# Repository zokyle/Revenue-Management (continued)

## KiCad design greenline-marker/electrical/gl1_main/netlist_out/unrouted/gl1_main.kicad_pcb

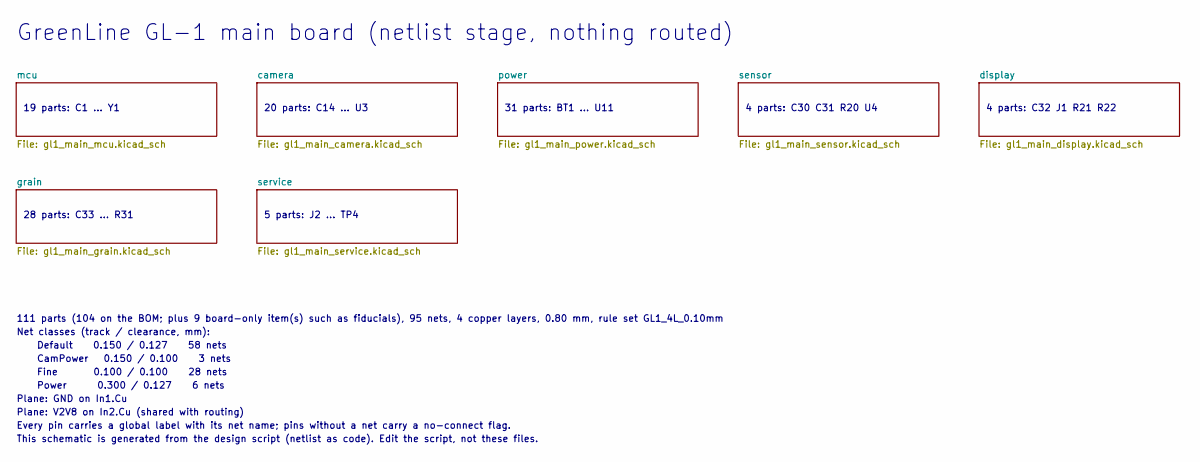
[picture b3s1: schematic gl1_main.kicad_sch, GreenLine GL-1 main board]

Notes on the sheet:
GreenLine GL-1 main board (netlist stage, nothing routed)
19 parts: C1 ... Y1
20 parts: C14 ... U3
31 parts: BT1 ... U11
4 parts: C30 C31 R20 U4
4 parts: C32 J1 R21 R22
28 parts: C33 ... R31
5 parts: J2 ... TP4
111 parts (104 on the BOM; plus 9 board-only item(s) such as fiducials), 95 nets, 4 copper layers, 0.80 mm, rule set GL1_4L_0.10mm
Net classes (track / clearance, mm):
Default 0.150 / 0.127 58 nets
CamPower 0.150 / 0.100 3 nets
Fine 0.100 / 0.100 28 nets
Power 0.300 / 0.127 6 nets
Plane: GND on In1.Cu
Plane: V2V8 on In2.Cu (shared with routing)
Every pin carries a global label with its net name; pins without a net carry a no-connect flag.
This schematic is generated from the design script (netlist as code). Edit the script, not these files.

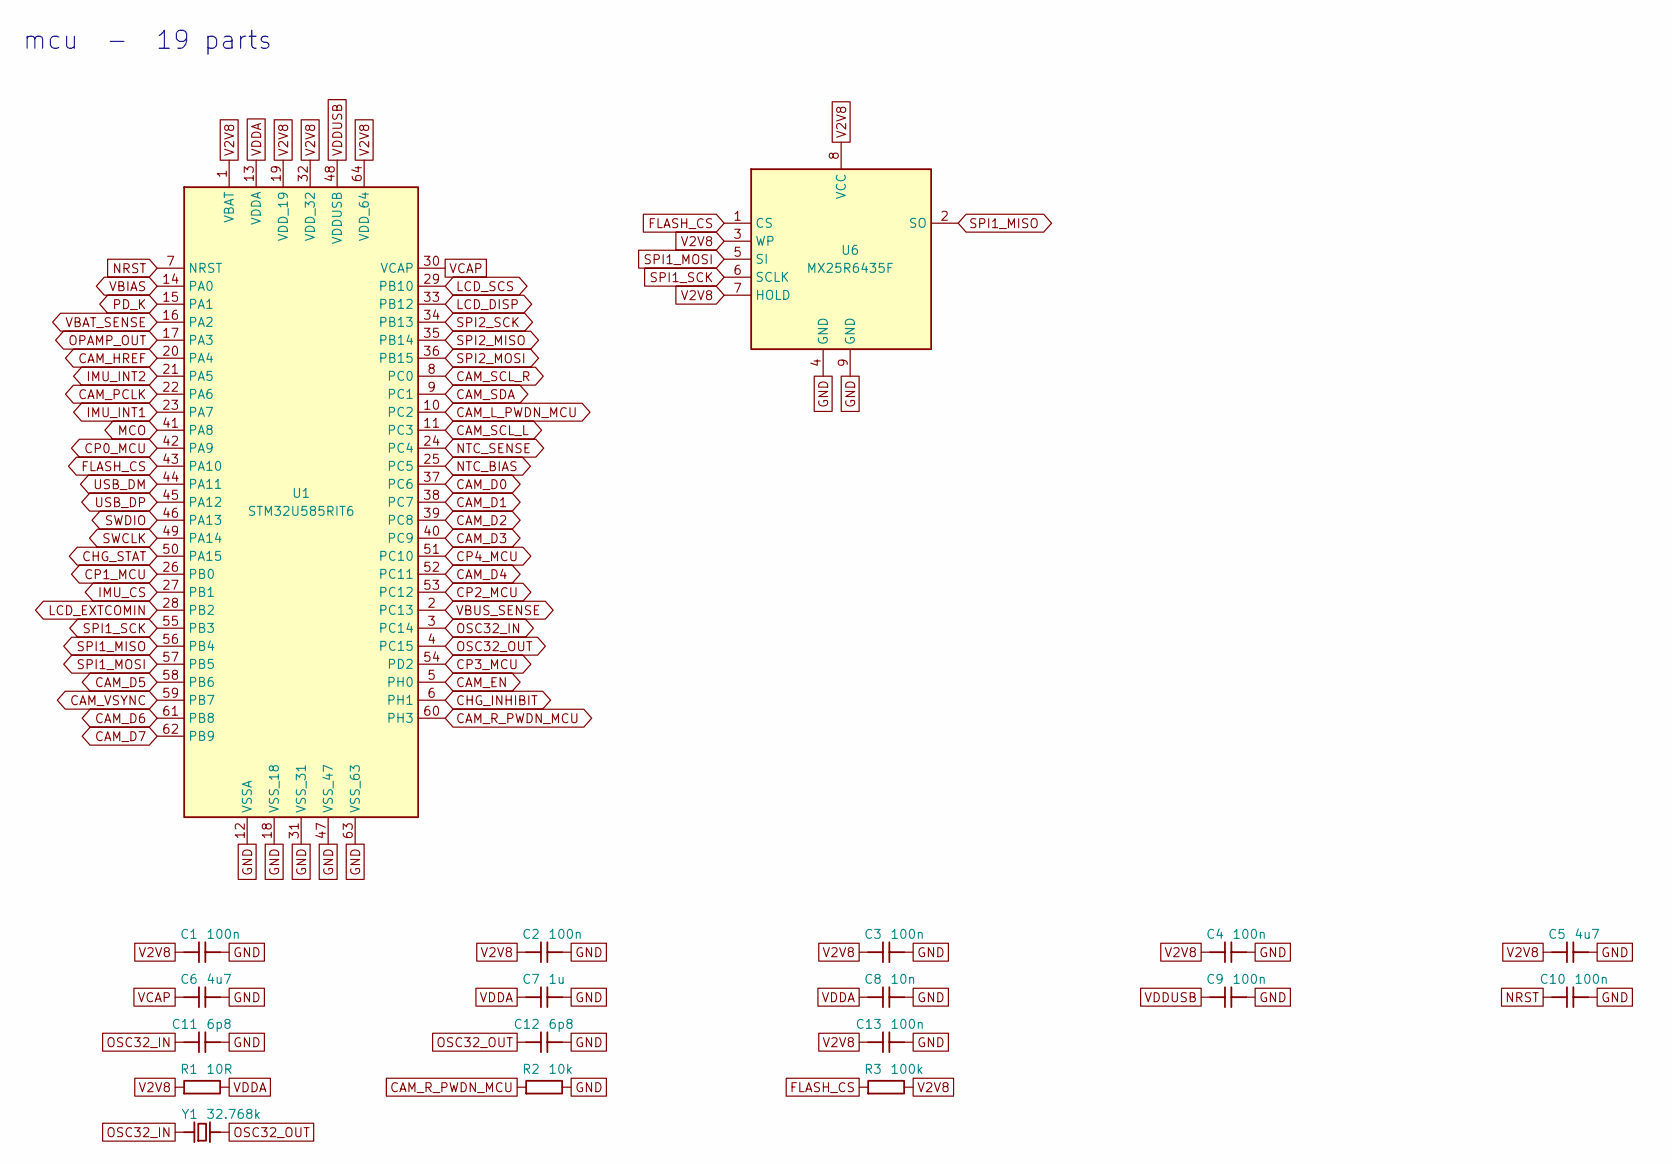
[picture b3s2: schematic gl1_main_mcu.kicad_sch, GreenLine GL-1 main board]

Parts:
C1, C2, C3, C4, C9, C10, C13: 100n; C_0402_1005Metric; MPN GRM155R71C104KA88D
C5, C6: 4u7; C_0402_1005Metric; MPN GRM155R60J475ME47D
C7: 1u; C_0402_1005Metric; MPN GRM155R61A105KE15D
C8: 10n; C_0402_1005Metric; MPN GRM155R71H103KA88D
C11, C12: 6p8; C_0402_1005Metric; MPN GRM1555C1H6R8CA01D
R1: 10R; R_0402_1005Metric; MPN RC0402FR-0710RL
R2: 10k; R_0402_1005Metric; MPN RC0402FR-0710KL
R3: 100k; R_0402_1005Metric; MPN RC0402FR-07100KL
U1: STM32U585RIT6; LQFP-64_10x10mm_P0.5mm; MPN STM32U585RIT6
U6: MX25R6435F; WSON-8-1EP_6x5mm_P1.27mm_EP3.4x4mm; MPN MX25R6435FZNIL0
Y1: 32.768k; Crystal_SMD_3215-2Pin_3.2x1.5mm; MPN ABS07-120-32.768KHZ-T

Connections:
CAM_D0: U1.37 (PC6); also elsewhere on the board
CAM_D1: U1.38 (PC7); also elsewhere on the board
CAM_D2: U1.39 (PC8); also elsewhere on the board
CAM_D3: U1.40 (PC9); also elsewhere on the board
CAM_D4: U1.52 (PC11); also elsewhere on the board
CAM_D5: U1.58 (PB6); also elsewhere on the board
CAM_D6: U1.61 (PB8); also elsewhere on the board
CAM_D7: U1.62 (PB9); also elsewhere on the board
CAM_EN: U1.5 (PH0); also elsewhere on the board
CAM_HREF: U1.20 (PA4); also elsewhere on the board
CAM_L_PWDN_MCU: U1.10 (PC2); also elsewhere on the board
CAM_PCLK: U1.22 (PA6); also elsewhere on the board
CAM_R_PWDN_MCU: R2.1, U1.60 (PH3); also elsewhere on the board
CAM_SCL_L: U1.11 (PC3); also elsewhere on the board
CAM_SCL_R: U1.8 (PC0); also elsewhere on the board
CAM_SDA: U1.9 (PC1); also elsewhere on the board
CAM_VSYNC: U1.59 (PB7); also elsewhere on the board
CHG_INHIBIT: U1.6 (PH1); also elsewhere on the board
CHG_STAT: U1.50 (PA15); also elsewhere on the board
CP0_MCU: U1.42 (PA9); also elsewhere on the board
CP1_MCU: U1.26 (PB0); also elsewhere on the board
CP2_MCU: U1.53 (PC12); also elsewhere on the board
CP3_MCU: U1.54 (PD2); also elsewhere on the board
CP4_MCU: U1.51 (PC10); also elsewhere on the board
FLASH_CS: R3.1, U1.43 (PA10), U6.1 (CS)
GND: C1.2, C2.2, C3.2, C4.2, C5.2, C6.2, C7.2, C8.2, C9.2, C10.2, C11.2, C12.2, C13.2, R2.2, U1.12 (VSSA), U1.18 (VSS_18), U1.31 (VSS_31), U1.47 (VSS_47), U1.63 (VSS_63), U6.4 (GND), U6.9 (GND); also elsewhere on the board
IMU_CS: U1.27 (PB1); also elsewhere on the board
IMU_INT1: U1.23 (PA7); also elsewhere on the board
IMU_INT2: U1.21 (PA5); also elsewhere on the board
LCD_DISP: U1.33 (PB12); also elsewhere on the board
LCD_EXTCOMIN: U1.28 (PB2); also elsewhere on the board
LCD_SCS: U1.29 (PB10); also elsewhere on the board
MCO: U1.41 (PA8); also elsewhere on the board
NRST: C10.1, U1.7 (NRST); also elsewhere on the board
NTC_BIAS: U1.25 (PC5); also elsewhere on the board
NTC_SENSE: U1.24 (PC4); also elsewhere on the board
OPAMP_OUT: U1.17 (PA3); also elsewhere on the board
OSC32_IN: C11.1, U1.3 (PC14), Y1.1
OSC32_OUT: C12.1, U1.4 (PC15), Y1.2
PD_K: U1.15 (PA1); also elsewhere on the board
SPI1_MISO: U1.56 (PB4), U6.2 (SO)
SPI1_MOSI: U1.57 (PB5), U6.5 (SI); also elsewhere on the board
SPI1_SCK: U1.55 (PB3), U6.6 (SCLK); also elsewhere on the board
SPI2_MISO: U1.35 (PB14); also elsewhere on the board
SPI2_MOSI: U1.36 (PB15); also elsewhere on the board
SPI2_SCK: U1.34 (PB13); also elsewhere on the board
SWCLK: U1.49 (PA14); also elsewhere on the board
SWDIO: U1.46 (PA13); also elsewhere on the board
USB_DM: U1.44 (PA11); also elsewhere on the board
USB_DP: U1.45 (PA12); also elsewhere on the board
V2V8: C1.1, C2.1, C3.1, C4.1, C5.1, C13.1, R1.1, R3.2, U1.1 (VBAT), U1.19 (VDD_19), U1.32 (VDD_32), U1.64 (VDD_64), U6.3 (WP), U6.7 (HOLD), U6.8 (VCC); also elsewhere on the board
VBAT_SENSE: U1.16 (PA2); also elsewhere on the board
VBIAS: U1.14 (PA0); also elsewhere on the board
VBUS_SENSE: U1.2 (PC13); also elsewhere on the board
VCAP: C6.1, U1.30 (VCAP)
VDDA: C7.1, C8.1, R1.2, U1.13 (VDDA)
VDDUSB: C9.1, U1.48 (VDDUSB); also elsewhere on the board

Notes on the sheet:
mcu - 19 parts

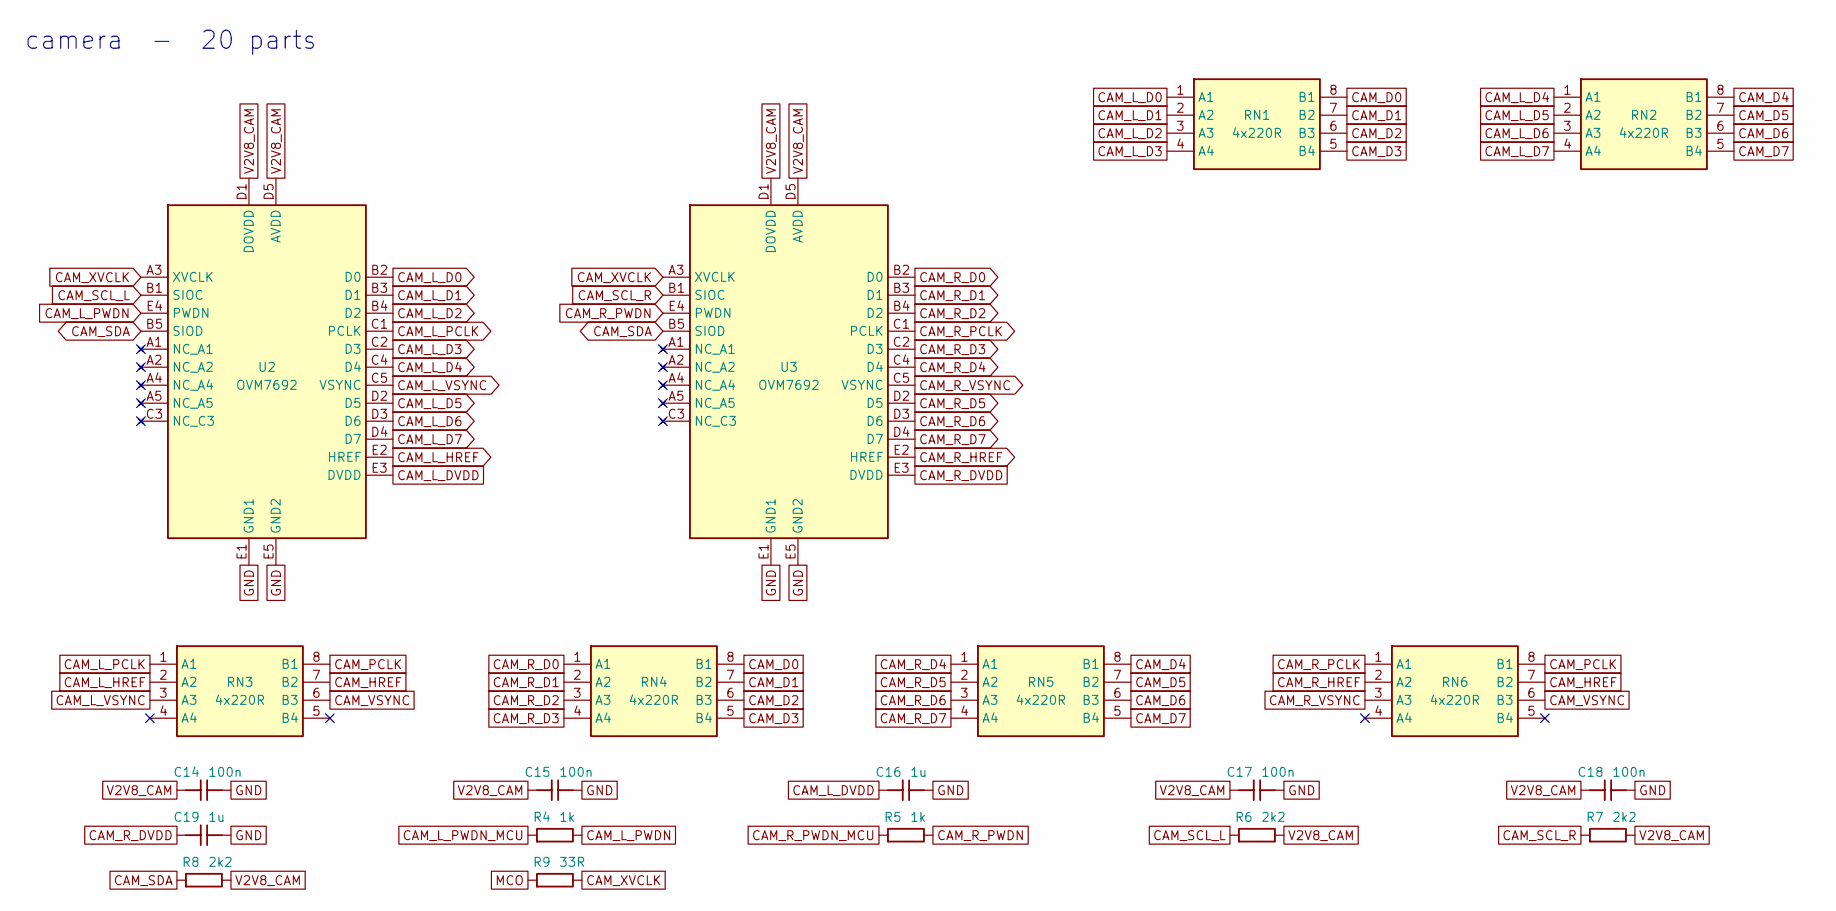
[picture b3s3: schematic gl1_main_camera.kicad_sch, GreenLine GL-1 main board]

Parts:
C14, C15, C17, C18: 100n; C_0402_1005Metric; MPN GRM155R71C104KA88D
C16, C19: 1u; C_0402_1005Metric; MPN GRM155R61A105KE15D
R4, R5: 1k; R_0402_1005Metric; MPN RC0402FR-071KL
R6, R7, R8: 2k2; R_0402_1005Metric; MPN RC0402FR-072K2L
R9: 33R; R_0402_1005Metric; MPN RC0402FR-0733RL
RN1, RN2, RN3, RN4, RN5, RN6: 4x220R; R_Array_Convex_4x0402; MPN EXB-28V221JX
U2, U3: OVM7692; OVM7692_BGA25_P0.5_PROVISIONAL; MPN OVM7692-RYAA

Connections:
CAM_D0: RN1.8 (B1), RN4.8 (B1); also elsewhere on the board
CAM_D1: RN1.7 (B2), RN4.7 (B2); also elsewhere on the board
CAM_D2: RN1.6 (B3), RN4.6 (B3); also elsewhere on the board
CAM_D3: RN1.5 (B4), RN4.5 (B4); also elsewhere on the board
CAM_D4: RN2.8 (B1), RN5.8 (B1); also elsewhere on the board
CAM_D5: RN2.7 (B2), RN5.7 (B2); also elsewhere on the board
CAM_D6: RN2.6 (B3), RN5.6 (B3); also elsewhere on the board
CAM_D7: RN2.5 (B4), RN5.5 (B4); also elsewhere on the board
CAM_HREF: RN3.7 (B2), RN6.7 (B2); also elsewhere on the board
CAM_L_D0: RN1.1 (A1), U2.B2 (D0)
CAM_L_D1: RN1.2 (A2), U2.B3 (D1)
CAM_L_D2: RN1.3 (A3), U2.B4 (D2)
CAM_L_D3: RN1.4 (A4), U2.C2 (D3)
CAM_L_D4: RN2.1 (A1), U2.C4 (D4)
CAM_L_D5: RN2.2 (A2), U2.D2 (D5)
CAM_L_D6: RN2.3 (A3), U2.D3 (D6)
CAM_L_D7: RN2.4 (A4), U2.D4 (D7)
CAM_L_DVDD: C16.1, U2.E3 (DVDD)
CAM_L_HREF: RN3.2 (A2), U2.E2 (HREF)
CAM_L_PCLK: RN3.1 (A1), U2.C1 (PCLK)
CAM_L_PWDN: R4.2, U2.E4 (PWDN)
CAM_L_PWDN_MCU: R4.1; also elsewhere on the board
CAM_L_VSYNC: RN3.3 (A3), U2.C5 (VSYNC)
CAM_PCLK: RN3.8 (B1), RN6.8 (B1); also elsewhere on the board
CAM_R_D0: RN4.1 (A1), U3.B2 (D0)
CAM_R_D1: RN4.2 (A2), U3.B3 (D1)
CAM_R_D2: RN4.3 (A3), U3.B4 (D2)
CAM_R_D3: RN4.4 (A4), U3.C2 (D3)
CAM_R_D4: RN5.1 (A1), U3.C4 (D4)
CAM_R_D5: RN5.2 (A2), U3.D2 (D5)
CAM_R_D6: RN5.3 (A3), U3.D3 (D6)
CAM_R_D7: RN5.4 (A4), U3.D4 (D7)
CAM_R_DVDD: C19.1, U3.E3 (DVDD)
CAM_R_HREF: RN6.2 (A2), U3.E2 (HREF)
CAM_R_PCLK: RN6.1 (A1), U3.C1 (PCLK)
CAM_R_PWDN: R5.2, U3.E4 (PWDN)
CAM_R_PWDN_MCU: R5.1; also elsewhere on the board
CAM_R_VSYNC: RN6.3 (A3), U3.C5 (VSYNC)
CAM_SCL_L: R6.1, U2.B1 (SIOC); also elsewhere on the board
CAM_SCL_R: R7.1, U3.B1 (SIOC); also elsewhere on the board
CAM_SDA: R8.1, U2.B5 (SIOD), U3.B5 (SIOD); also elsewhere on the board
CAM_VSYNC: RN3.6 (B3), RN6.6 (B3); also elsewhere on the board
CAM_XVCLK: R9.2, U2.A3 (XVCLK), U3.A3 (XVCLK)
GND: C14.2, C15.2, C16.2, C17.2, C18.2, C19.2, U2.E1 (GND1), U2.E5 (GND2), U3.E1 (GND1), U3.E5 (GND2); also elsewhere on the board
MCO: R9.1; also elsewhere on the board
V2V8_CAM: C14.1, C15.1, C17.1, C18.1, R6.2, R7.2, R8.2, U2.D1 (DOVDD), U2.D5 (AVDD), U3.D1 (DOVDD), U3.D5 (AVDD); also elsewhere on the board

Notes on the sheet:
camera - 20 parts

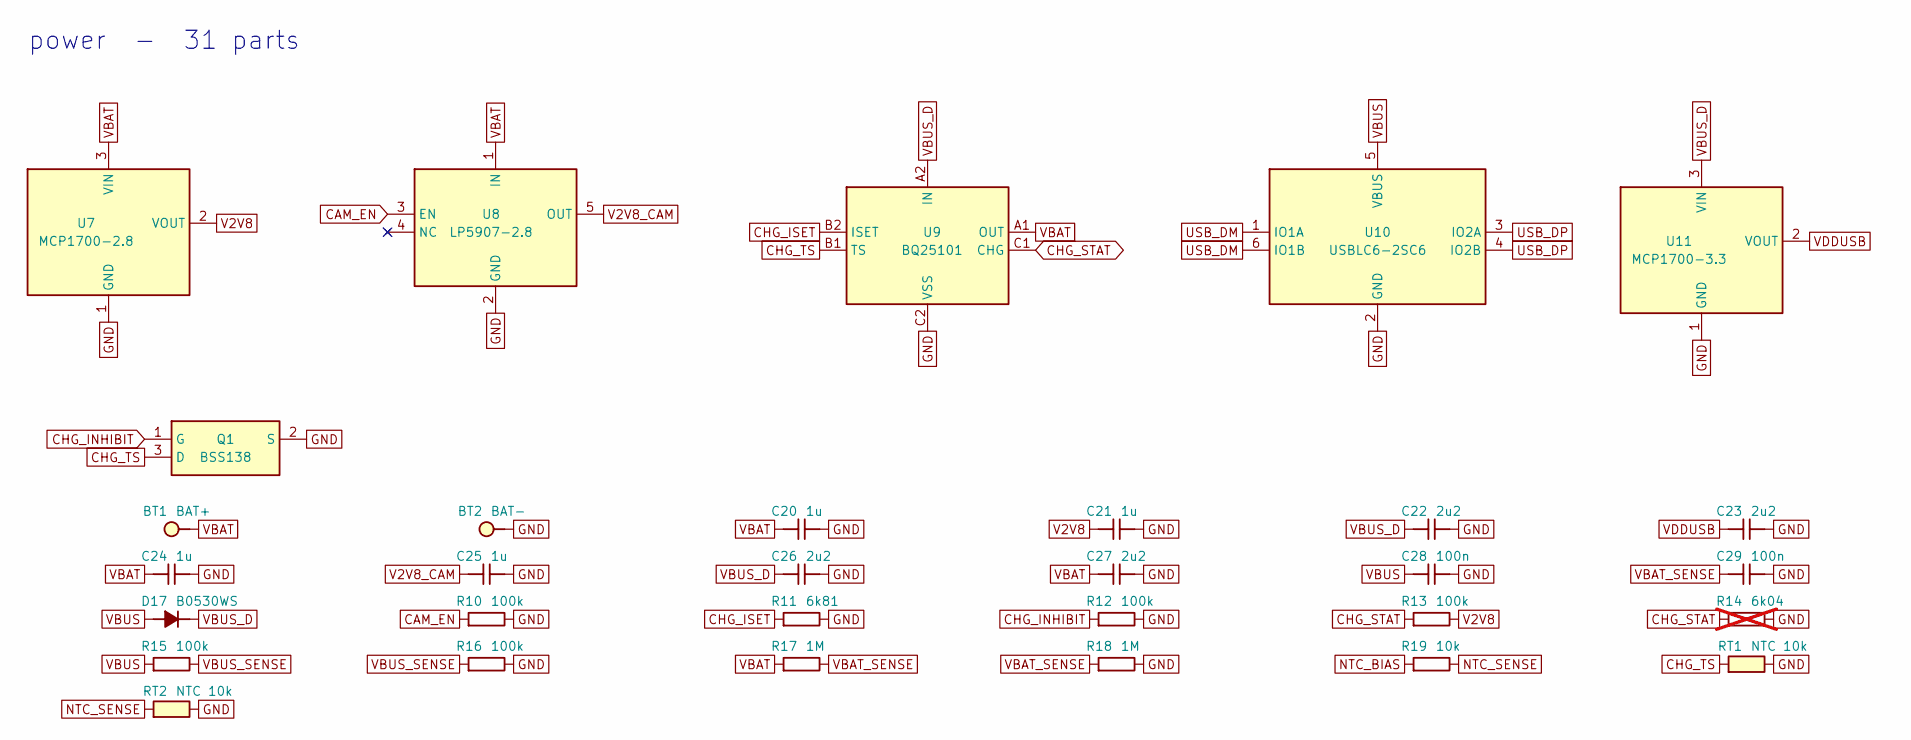
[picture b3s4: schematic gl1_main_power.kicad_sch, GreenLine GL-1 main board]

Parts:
BT1: BAT+; BatteryTab_1.5x2.4mm
BT2: BAT-; BatteryTab_1.5x2.4mm
C20, C21, C24, C25: 1u; C_0402_1005Metric; MPN GRM155R61A105KE15D
C22, C23, C26, C27: 2u2; C_0402_1005Metric; MPN GRM155R61A225KE95D
C28, C29: 100n; C_0402_1005Metric; MPN GRM155R71C104KA88D
D17: B0530WS; D_SOD-323; MPN B0530WS-7-F
Q1: BSS138; SOT-23; MPN BSS138LT1G
R10, R12, R13, R15, R16: 100k; R_0402_1005Metric; MPN RC0402FR-07100KL
R11: 6k81; R_0402_1005Metric; MPN RC0402FR-076K81L
R14: 6k04; R_0402_1005Metric; MPN RC0402FR-076K04L; not fitted
R17, R18: 1M; R_0402_1005Metric; MPN RC0402FR-071ML
R19: 10k; R_0402_1005Metric; MPN RC0402FR-0710KL
RT1, RT2: NTC 10k; R_0402_1005Metric; MPN NCU15XH103F60RC
U7: MCP1700-2.8; SOT-23; MPN MCP1700T-2802E/TT
U8: LP5907-2.8; SOT-23-5; MPN LP5907MFX-2.8/NOPB
U9: BQ25101; BQ25101_YFP_DSBGA6_P0.4_PROVISIONAL; MPN BQ25101YFPR
U10: USBLC6-2SC6; SOT-23-6; MPN USBLC6-2SC6
U11: MCP1700-3.3; SOT-23; MPN MCP1700T-3302E/TT

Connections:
CAM_EN: R10.1, U8.3 (EN); also elsewhere on the board
CHG_INHIBIT: Q1.1 (G), R12.1; also elsewhere on the board
CHG_ISET: R11.1, U9.B2 (ISET)
CHG_STAT: R13.1, R14.1, U9.C1 (CHG); also elsewhere on the board
CHG_TS: Q1.3 (D), RT1.1, U9.B1 (TS)
GND: BT2.1, C20.2, C21.2, C22.2, C23.2, C24.2, C25.2, C26.2, C27.2, C28.2, C29.2, Q1.2 (S), R10.2, R11.2, R12.2, R14.2, R16.2, R18.2, RT1.2, RT2.2, U7.1 (GND), U8.2 (GND), U9.C2 (VSS), U10.2 (GND), U11.1 (GND); also elsewhere on the board
NTC_BIAS: R19.1; also elsewhere on the board
NTC_SENSE: R19.2, RT2.1; also elsewhere on the board
USB_DM: U10.1 (IO1A), U10.6 (IO1B); also elsewhere on the board
USB_DP: U10.3 (IO2A), U10.4 (IO2B); also elsewhere on the board
V2V8: C21.1, R13.2, U7.2 (VOUT); also elsewhere on the board
V2V8_CAM: C25.1, U8.5 (OUT); also elsewhere on the board
VBAT: BT1.1, C20.1, C24.1, C27.1, R17.1, U7.3 (VIN), U8.1 (IN), U9.A1 (OUT); also elsewhere on the board
VBAT_SENSE: C29.1, R17.2, R18.1; also elsewhere on the board
VBUS: C28.1, D17.2 (A), R15.1, U10.5 (VBUS); also elsewhere on the board
VBUS_D: C22.1, C26.1, D17.1 (K), U9.A2 (IN), U11.3 (VIN)
VBUS_SENSE: R15.2, R16.1; also elsewhere on the board
VDDUSB: C23.1, U11.2 (VOUT); also elsewhere on the board

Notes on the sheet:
power - 31 parts

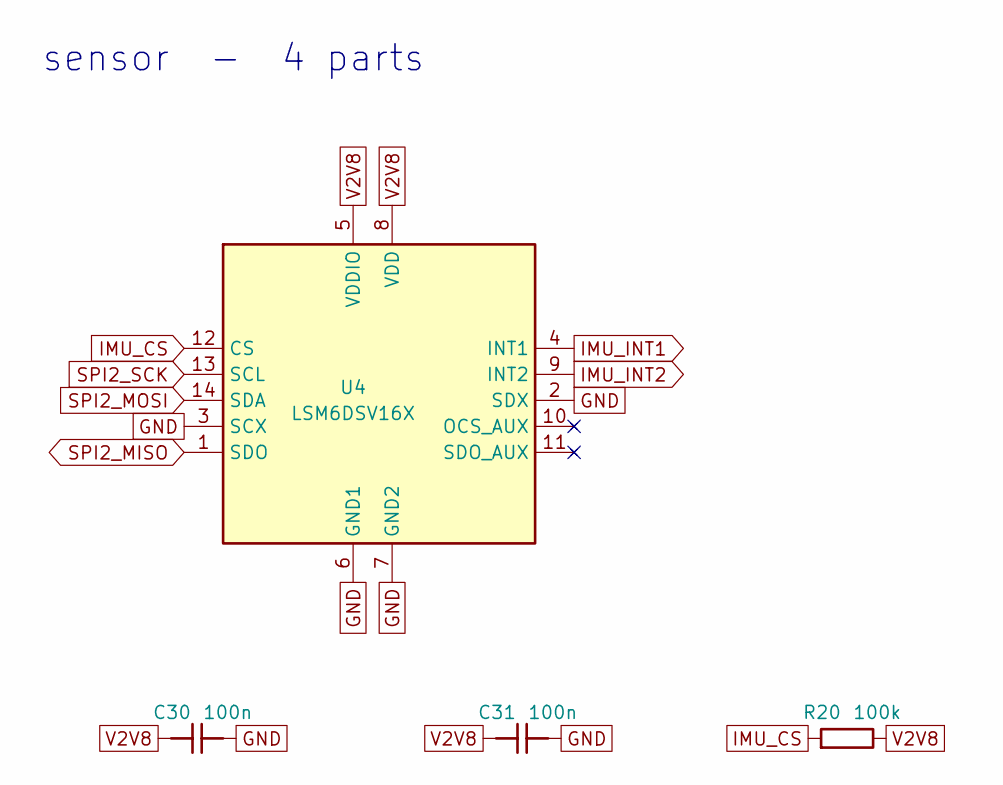
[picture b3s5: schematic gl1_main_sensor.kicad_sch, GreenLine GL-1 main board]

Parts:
C30, C31: 100n; C_0402_1005Metric; MPN GRM155R71C104KA88D
R20: 100k; R_0402_1005Metric; MPN RC0402FR-07100KL
U4: LSM6DSV16X; LGA-14_3x2.5mm_P0.5mm_LayoutBorder3x4y; MPN LSM6DSV16XTR

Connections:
GND: C30.2, C31.2, U4.2 (SDX), U4.3 (SCX), U4.6 (GND1), U4.7 (GND2); also elsewhere on the board
IMU_CS: R20.1, U4.12 (CS); also elsewhere on the board
IMU_INT1: U4.4 (INT1); also elsewhere on the board
IMU_INT2: U4.9 (INT2); also elsewhere on the board
SPI2_MISO: U4.1 (SDO); also elsewhere on the board
SPI2_MOSI: U4.14 (SDA); also elsewhere on the board
SPI2_SCK: U4.13 (SCL); also elsewhere on the board
V2V8: C30.1, C31.1, R20.2, U4.5 (VDDIO), U4.8 (VDD); also elsewhere on the board

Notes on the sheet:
sensor - 4 parts

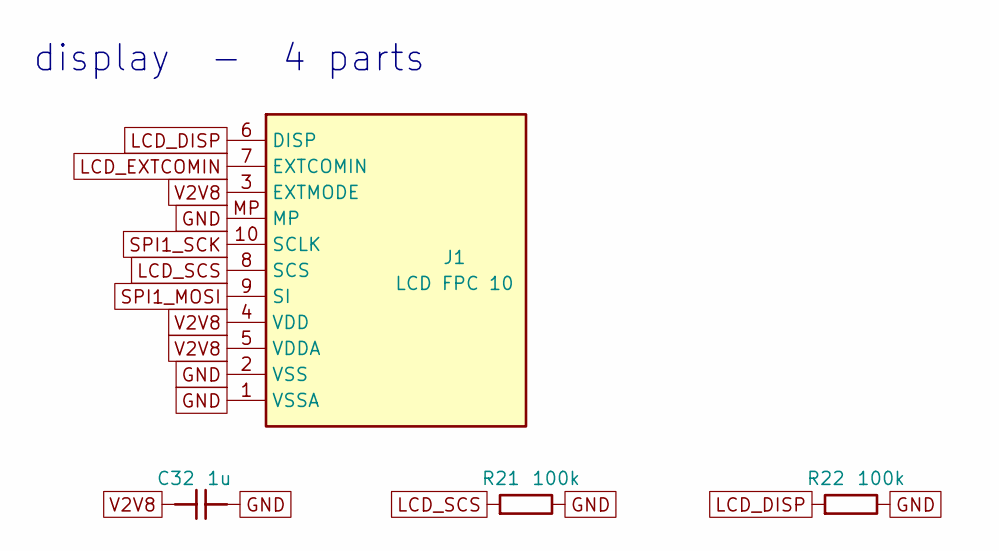
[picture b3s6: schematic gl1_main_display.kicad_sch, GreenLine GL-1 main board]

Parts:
C32: 1u; C_0402_1005Metric; MPN GRM155R61A105KE15D
J1: LCD FPC 10; Hirose_FH12-10S-0.5SH_1x10-1MP_P0.50mm_Horizontal; MPN FH12A-10S-0.5SH(55)
R21, R22: 100k; R_0402_1005Metric; MPN RC0402FR-07100KL

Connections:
GND: C32.2, J1.1 (VSSA), J1.2 (VSS), J1.MP, R21.2, R22.2; also elsewhere on the board
LCD_DISP: J1.6 (DISP), R22.1; also elsewhere on the board
LCD_EXTCOMIN: J1.7 (EXTCOMIN); also elsewhere on the board
LCD_SCS: J1.8 (SCS), R21.1; also elsewhere on the board
SPI1_MOSI: J1.9 (SI); also elsewhere on the board
SPI1_SCK: J1.10 (SCLK); also elsewhere on the board
V2V8: C32.1, J1.3 (EXTMODE), J1.4 (VDD), J1.5 (VDDA); also elsewhere on the board

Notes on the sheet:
display - 4 parts

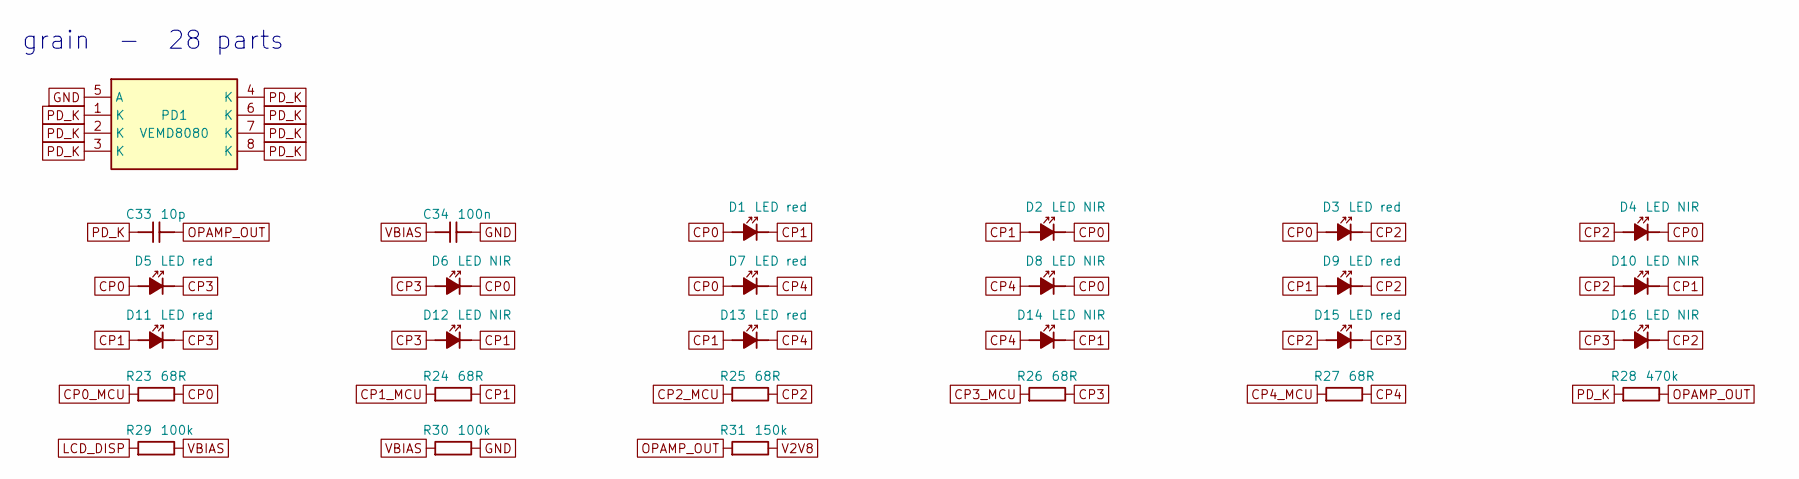
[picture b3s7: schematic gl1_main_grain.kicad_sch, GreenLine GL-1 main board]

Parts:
C33: 10p; C_0402_1005Metric; MPN GRM1555C1H100JA01D
C34: 100n; C_0402_1005Metric; MPN GRM155R71C104KA88D
D1, D3, D5, D7, D9, D11, D13, D15: LED red; LED_0402_1005Metric; MPN VLMS1500-GS08
D2, D4, D6, D8, D10, D12, D14, D16: LED NIR; LED_0402_1005Metric; MPN SFH 4053B
PD1: VEMD8080; VEMD8080_4.8x2.5mm_PROVISIONAL; MPN VEMD8080
R23, R24, R25, R26, R27: 68R; R_0402_1005Metric; MPN RC0402FR-0768RL
R28: 470k; R_0402_1005Metric; MPN RC0402FR-07470KL
R29, R30: 100k; R_0402_1005Metric; MPN RC0402FR-07100KL
R31: 150k; R_0402_1005Metric; MPN RC0402FR-07150KL

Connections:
CP0: D1.2 (A), D2.1 (K), D3.2 (A), D4.1 (K), D5.2 (A), D6.1 (K), D7.2 (A), D8.1 (K), R23.2
CP0_MCU: R23.1; also elsewhere on the board
CP1: D1.1 (K), D2.2 (A), D9.2 (A), D10.1 (K), D11.2 (A), D12.1 (K), D13.2 (A), D14.1 (K), R24.2
CP1_MCU: R24.1; also elsewhere on the board
CP2: D3.1 (K), D4.2 (A), D9.1 (K), D10.2 (A), D15.2 (A), D16.1 (K), R25.2
CP2_MCU: R25.1; also elsewhere on the board
CP3: D5.1 (K), D6.2 (A), D11.1 (K), D12.2 (A), D15.1 (K), D16.2 (A), R26.2
CP3_MCU: R26.1; also elsewhere on the board
CP4: D7.1 (K), D8.2 (A), D13.1 (K), D14.2 (A), R27.2
CP4_MCU: R27.1; also elsewhere on the board
GND: C34.2, PD1.5 (A), R30.2; also elsewhere on the board
LCD_DISP: R29.1; also elsewhere on the board
OPAMP_OUT: C33.2, R28.2, R31.1; also elsewhere on the board
PD_K: C33.1, PD1.1 (K), PD1.2 (K), PD1.3 (K), PD1.4 (K), PD1.6 (K), PD1.7 (K), PD1.8 (K), R28.1; also elsewhere on the board
V2V8: R31.2; also elsewhere on the board
VBIAS: C34.1, R29.2, R30.1; also elsewhere on the board

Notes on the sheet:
grain - 28 parts

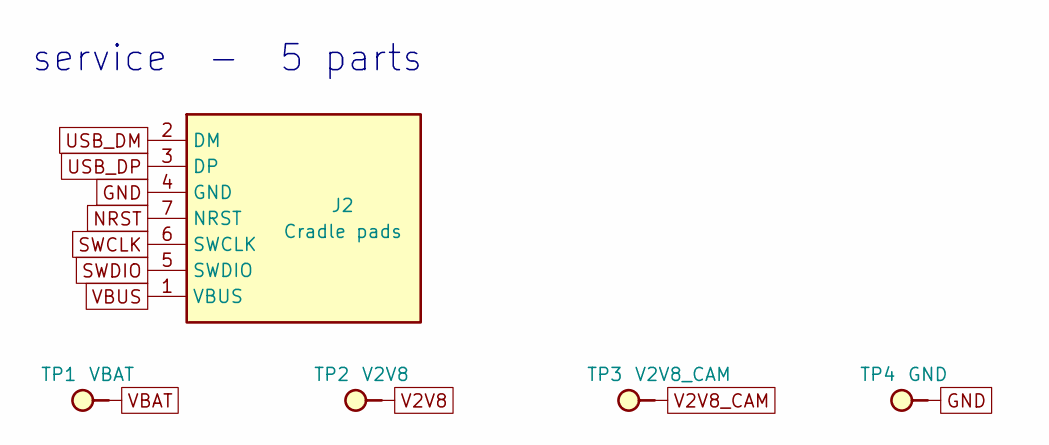
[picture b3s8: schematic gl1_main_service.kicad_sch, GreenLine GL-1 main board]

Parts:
J2: Cradle pads; ContactRow_7x1.8mm_P2.54
TP1: VBAT; TestPad_D1mm
TP2: V2V8; TestPad_D1mm
TP3: V2V8_CAM; TestPad_D1mm
TP4: GND; TestPad_D1mm

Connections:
GND: J2.4 (GND), TP4.1; also elsewhere on the board
NRST: J2.7 (NRST); also elsewhere on the board
SWCLK: J2.6 (SWCLK); also elsewhere on the board
SWDIO: J2.5 (SWDIO); also elsewhere on the board
USB_DM: J2.2 (DM); also elsewhere on the board
USB_DP: J2.3 (DP); also elsewhere on the board
V2V8: TP2.1; also elsewhere on the board
V2V8_CAM: TP3.1; also elsewhere on the board
VBAT: TP1.1; also elsewhere on the board
VBUS: J2.1 (VBUS); also elsewhere on the board

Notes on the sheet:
service - 5 parts

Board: 4 copper layers, 121 parts (24 on the bottom side), 95 nets, no tracks yet.

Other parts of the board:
FID1, FID2, FID3, FID4, FID5, FID6: Fiducial; Fiducial_1mm_Mask2mm
FL1, FL2, FL3: Ball-foot land; BallFootLand_D1.6mm
H1: NPTH 1.15mm; NPTH_1.15mm

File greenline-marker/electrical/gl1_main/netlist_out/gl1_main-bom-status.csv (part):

Item,Qty,References,Value,Description,Footprint,MPN,Manufacturer,Distributor,Distributor PN,Unit Price,DNP,Status,Status note
1,16,C1 C2 C3 C4 C9 C10 C13 C14 C15 C17 C18 C28 C29 C30 C31 C34,100n,MLCC 0402 100 nF 16 V X7R,Capacitor_SMD:C_0402_1005Metric,GRM155R71C104KA88D,Murata,any authorised distributor (order by MPN),GRM155R71C104KA88D,,,PROVISIONAL,MPN from memory; value per DESIGN_SPEC / NETLIST_NOTES
2,2,C5 C6,4u7,MLCC 0402 4.7 uF 6.3 V X5R,Capacitor_SMD:C_0402_1005Metric,GRM155R60J475ME47D,Murata,any authorised distributor (order by MPN),GRM155R60J475ME47D,,,PROVISIONAL,MPN from memory; value per DESIGN_SPEC / NETLIST_NOTES
3,8,C7 C16 C19 C20 C21 C24 C25 C32,1u,MLCC 0402 1 uF 10 V X5R,Capacitor_SMD:C_0402_1005Metric,GRM155R61A105KE15D,Murata,any authorised distributor (order by MPN),GRM155R61A105KE15D,,,PROVISIONAL,MPN from memory; value per DESIGN_SPEC / NETLIST_NOTES
4,1,C8,10n,MLCC 0402 10 nF 50 V X7R,Capacitor_SMD:C_0402_1005Metric,GRM155R71H103KA88D,Murata,any authorised distributor (order by MPN),GRM155R71H103KA88D,,,PROVISIONAL,MPN from memory; value per DESIGN_SPEC / NETLIST_NOTES
5,2,C11 C12,6p8,MLCC 0402 6.8 pF 50 V C0G +-0.25 pF,Capacitor_SMD:C_0402_1005Metric,GRM1555C1H6R8CA01D,Murata,any authorised distributor (order by MPN),GRM1555C1H6R8CA01D,,,PROVISIONAL,MPN from memory; value per DESIGN_SPEC / NETLIST_NOTES
6,4,C22 C23 C26 C27,2u2,MLCC 0402 2.2 uF 10 V X5R,Capacitor_SMD:C_0402_1005Metric,GRM155R61A225KE95D,Murata,any authorised distributor (order by MPN),GRM155R61A225KE95D,,,PROVISIONAL,MPN from memory; value per DESIGN_SPEC / NETLIST_NOTES
7,1,C33,10p,MLCC 0402 10 pF 50 V C0G 5 %,Capacitor_SMD:C_0402_1005Metric,GRM1555C1H100JA01D,Murata,any authorised distributor (order by MPN),GRM1555C1H100JA01D,,,PROVISIONAL,MPN from memory; value per DESIGN_SPEC / NETLIST_NOTES
8,8,D1 D3 D5 D7 D9 D11 D13 D15,LED red,LED super red 631 nm 0402,LED_SMD:LED_0402_1005Metric,VLMS1500-GS08,Vishay,any authorised distributor (order by MPN),VLMS1500-GS08,,,PROVISIONAL,"MPN research-confirmed; land pattern is the generic KiCad 0402 LED, polarity mark and pad sizes not checked"
9,8,D2 D4 D6 D8 D10 D12 D14 D16,LED NIR,LED 850 nm 0402 (alternative: Inolux IN-S42CTQIR),LED_SMD:LED_0402_1005Metric,SFH 4053B,ams OSRAM,any authorised distributor (order by MPN),SFH 4053B,,,PROVISIONAL,"MPN from DESIGN_SPEC E3 (successor of the SFH 4053; its data sheet has not been read); land pattern is the generic KiCad 0402 LED, polarity mark and pad sizes not checked"
10,1,D17,B0530WS,Schottky 30 V 0.5 A SOD-323 (VBUS pad to charger),Diode_SMD:D_SOD-323,B0530WS-7-F,Diodes Incorporated,Digi-Key,B0530WS-FDICT-ND,0.30,,RESEARCH,"MPN, ratings, Digi-Key PN research-confirmed; body height and VF at 25 mA not seen"
11,1,J1,LCD FPC 10,"FPC connector 10 x 0.5 mm, TOP contact, 2.0 mm high; PIN-1 EDGE OF THE TAIL PROVISIONAL (tail pin n on pad 11 - n)",Connector_FFC-FPC:Hirose_FH12-10S-0.5SH_1x10-1MP_P0.50mm_Horizontal,FH12A-10S-0.5SH(55),Hirose,Digi-Key,HFK110CT-ND,,,PROVISIONAL,"top-contact FH12A on the bottom-contact FH12 land pattern (spec); pin order and pin-1 edge of the tail PROVISIONAL (LCD_TAIL, LCD_TAIL_PIN1_EDGE); the body lies 1.5 mm behind the mechanical model's box (open item, NETLIST_NOTES 5.1); Digi-Key PN from docs/sourcing.csv"
12,1,PD1,VEMD8080,"PIN photodiode 4.5 mm2, 350-1100 nm; LAND PATTERN PROVISIONAL",gleda:VEMD8080_4.8x2.5mm_PROVISIONAL,VEMD8080,Vishay,any authorised distributor (order by MPN),VEMD8080,,,PROVISIONAL,"package research-confirmed; pad layout and anode pad from public footprints, not the Vishay drawing (VEMD8080_PADS)"
13,1,Q1,BSS138,"N-MOSFET 50 V, VGS(th) 1.5 V max, SOT-23 (pulls the charger's TS input low)",Package_TO_SOT_SMD:SOT-23,BSS138LT1G,onsemi,Digi-Key,product page 918376 (SKU not seen),,,PROVISIONAL,"part named in DESIGN_SPEC; order code from docs/sourcing.csv; pin order (G1 S2 D3), threshold and leakage from memory"
14,1,R1,10R,Resistor 0402 1 % 10R,Resistor_SMD:R_0402_1005Metric,RC0402FR-0710RL,Yageo,any authorised distributor (order by MPN),RC0402FR-0710RL,,,PROVISIONAL,MPN from memory; value per DESIGN_SPEC / NETLIST_NOTES
15,2,R2 R19,10k,Resistor 0402 1 % 10k,Resistor_SMD:R_0402_1005Metric,RC0402FR-0710KL,Yageo,any authorised distributor (order by MPN),RC0402FR-0710KL,,,PROVISIONAL,MPN from memory; value per DESIGN_SPEC / NETLIST_NOTES
16,11,R3 R10 R12 R13 R15 R16 R20 R21 R22 R29 R30,100k,Resistor 0402 1 % 100k,Resistor_SMD:R_0402_1005Metric,RC0402FR-07100KL,Yageo,any authorised distributor (order by MPN),RC0402FR-07100KL,,,PROVISIONAL,MPN from memory; value per DESIGN_SPEC / NETLIST_NOTES
17,2,R4 R5,1k,Resistor 0402 1 % 1k,Resistor_SMD:R_0402_1005Metric,RC0402FR-071KL,Yageo,any authorised distributor (order by MPN),RC0402FR-071KL,,,PROVISIONAL,MPN from memory; value per DESIGN_SPEC / NETLIST_NOTES
18,3,R6 R7 R8,2k2,Resistor 0402 1 % 2k2,Resistor_SMD:R_0402_1005Metric,RC0402FR-072K2L,Yageo,any authorised distributor (order by MPN),RC0402FR-072K2L,,,PROVISIONAL,MPN from memory; value per DESIGN_SPEC / NETLIST_NOTES
19,1,R9,33R,Resistor 0402 1 % 33R,Resistor_SMD:R_0402_1005Metric,RC0402FR-0733RL,Yageo,any authorised distributor (order by MPN),RC0402FR-0733RL,,,PROVISIONAL,MPN from memory; value per DESIGN_SPEC / NETLIST_NOTES
20,1,R11,6k81,Resistor 0402 1 % 6k81,Resistor_SMD:R_0402_1005Metric,RC0402FR-076K81L,Yageo,any authorised distributor (order by MPN),RC0402FR-076K81L,,,PROVISIONAL,MPN from memory; value per DESIGN_SPEC / NETLIST_NOTES
21,2,R17 R18,1M,Resistor 0402 1 % 1M,Resistor_SMD:R_0402_1005Metric,RC0402FR-071ML,Yageo,any authorised distributor (order by MPN),RC0402FR-071ML,,,PROVISIONAL,MPN from memory; value per DESIGN_SPEC / NETLIST_NOTES
22,5,R23 R24 R25 R26 R27,68R,Resistor 0402 1 % 68R,Resistor_SMD:R_0402_1005Metric,RC0402FR-0768RL,Yageo,any authorised distributor (order by MPN),RC0402FR-0768RL,,,PROVISIONAL,MPN from memory; value per DESIGN_SPEC / NETLIST_NOTES
23,1,R28,470k,Resistor 0402 1 % 470k,Resistor_SMD:R_0402_1005Metric,RC0402FR-07470KL,Yageo,any authorised distributor (order by MPN),RC0402FR-07470KL,,,PROVISIONAL,MPN from memory; value per DESIGN_SPEC / NETLIST_NOTES
24,1,R31,150k,Resistor 0402 1 % 150k,Resistor_SMD:R_0402_1005Metric,RC0402FR-07150KL,Yageo,any authorised distributor (order by MPN),RC0402FR-07150KL,,,PROVISIONAL,MPN from memory; value per DESIGN_SPEC / NETLIST_NOTES
25,6,RN1 RN2 RN3 RN4 RN5 RN6,4x220R,"Resistor array 4 x 220 ohm 5 %, 0402 x 4 (0804), convex",Resistor_SMD:R_Array_Convex_4x0402,EXB-28V221JX,Panasonic,Digi-Key,Y7221CT-ND,,,PROVISIONAL,MPN from DESIGN_SPEC (stock PROVISIONAL); Digi-Key PN from docs/sourcing.csv; height and the match of the KiCad 4x0402 convex land pattern not checked
26,2,RT1 RT2,NTC 10k,"NTC thermistor 10 kohm 1 %, B 3380 K, 0402 (cell temperature)",Resistor_SMD:R_0402_1005Metric,NCU15XH103F60RC,Murata,any authorised distributor (order by MPN),NCU15XH103F60RC,,,PROVISIONAL,"MPN from DESIGN_SPEC E2 (stock PROVISIONAL); B value as used by the firmware, no R-T table read; joined to the cell with thermal adhesive at assembly"
27,1,U1,STM32U585RIT6,"MCU Cortex-M33, 2 MB / 786 kB, LQFP-64 10 x 10 mm",Package_QFP:LQFP-64_10x10mm_P0.5mm,STM32U585RIT6,STMicroelectronics,Digi-Key,497-STM32U585RIT6-ND,,,RESEARCH,"MPN, package, pad map: research + ST open pin data; height 1.6 mm and every electrical limit: PROVISIONAL"
28,2,U2 U3,OVM7692,VGA camera cube 2.95 x 3.47 x 2.76 mm; BALL MAP PROVISIONAL (stand-in),gleda:OVM7692_BGA25_P0.5_PROVISIONAL,OVM7692-RYAA,OmniVision,Digi-Key,884-1027-1-ND,27.50,,PROVISIONAL,"MPN, size, Digi-Key PN research-confirmed; ball map, pitch, pad size, PWDN / tri-state behaviour NOT known"
29,1,U4,LSM6DSV16X,"6-axis IMU, LGA-14L 2.5 x 3.0 x 0.83 mm",Package_LGA:LGA-14_3x2.5mm_P0.5mm_LayoutBorder3x4y,LSM6DSV16XTR,STMicroelectronics,Digi-Key,497-LSM6DSV16XTRCT-ND,4.42,,RESEARCH,"MPN, package, pin map, Digi-Key PN research-confirmed; wiring of pins 2 and 3 and any INT1 power-on restriction: PROVISIONAL"
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
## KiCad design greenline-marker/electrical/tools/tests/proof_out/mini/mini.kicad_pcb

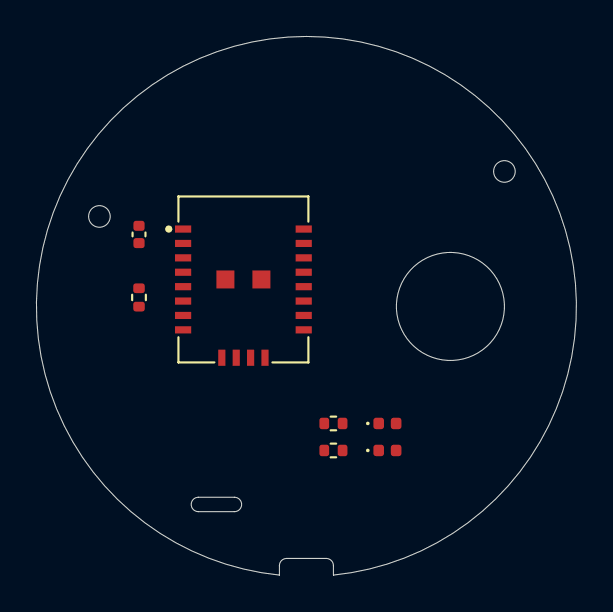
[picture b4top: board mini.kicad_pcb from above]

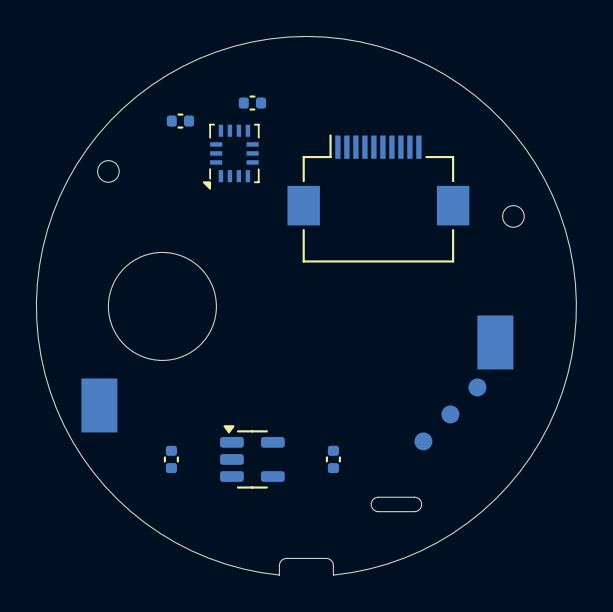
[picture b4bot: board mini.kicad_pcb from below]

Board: 4 copper layers, 30.0 x 29.9 mm, 21 parts (12 on the bottom side), 19 nets, no tracks yet.

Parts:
BT1: BAT+; BatteryTab_2x3mm
BT2: BAT-; BatteryTab_2x3mm
C1, C3, C4: 1u; C_0402_1005Metric
C2, C5: 100n; C_0402_1005Metric
D1, D2: LED; LED_0402_1005Metric
H1, H2: NPTH 1.2mm; NPTH_1.2mm
J1: FPC 10; Hirose_FH12-10S-0.5SH_1x10-1MP_P0.50mm_Horizontal
R1, R2: 1k; R_0402_1005Metric
R3: 10k; R_0402_1005Metric
TP1, TP2, TP3: TP; TestPad_D1mm
U1: MiniModule; MiniModule_7x9
U2: BMI270; Bosch_LGA-14_3x2.5mm_P0.5mm
U3: LDO 3V0; SOT-23-5

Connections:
+3V0: C1.1, C2.1, C4.1, C5.1, J1.2, R3.1, U1.2 (VDD), U2.5 (VDDIO), U2.8 (VDD), U3.5 (VOUT)
CAM_EN: J1.10, R3.2, U1.18 (EN)
D0: J1.6, U1.9 (D0)
D1: J1.7, U1.10 (D1)
D2: J1.8, U1.11 (D2)
D3: J1.9, U1.12 (D3)
GND: BT2.1, C1.2, C2.2, C3.2, C4.2, C5.2, D1.1 (K), D2.1 (K), J1.1, J1.MP, TP3.1, U1.1 (GND), U1.8 (GND), U1.13 (GND), U1.20 (GND), U1.21 (GND), U2.6 (GNDIO), U2.7 (GND), U3.2 (GND)
IMU_CS: U1.6 (CS), U2.12 (CSB)
IMU_INT: U1.7 (INT), U2.4 (INT1)
LED1: R1.1, U1.14 (LED1)
LED1_A: D1.2 (A), R1.2
LED2: R2.1, U1.15 (LED2)
LED2_A: D2.2 (A), R2.2
MISO: J1.5, U1.5 (MISO), U2.1 (SDO)
MOSI: J1.4, U1.4 (MOSI), U2.14 (SDX)
SCK: J1.3, U1.3 (SCK), U2.13 (SCX)
SWCLK: TP2.1, U1.17 (SWCLK)
SWDIO: TP1.1, U1.16 (SWDIO)
VBAT: BT1.1, C3.1, U3.1 (VIN), U3.3 (EN)
